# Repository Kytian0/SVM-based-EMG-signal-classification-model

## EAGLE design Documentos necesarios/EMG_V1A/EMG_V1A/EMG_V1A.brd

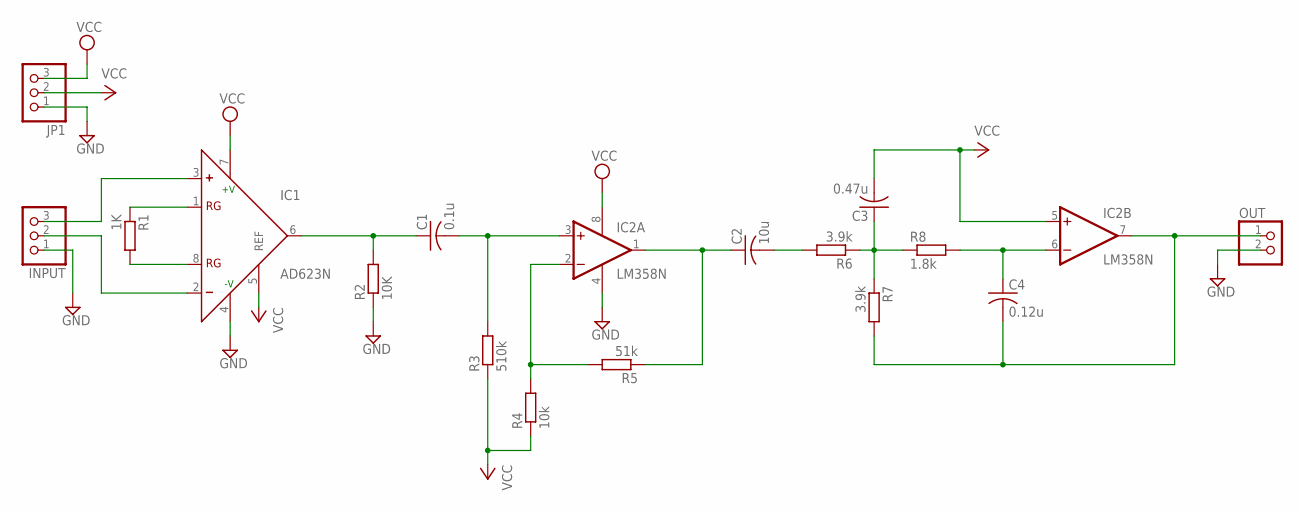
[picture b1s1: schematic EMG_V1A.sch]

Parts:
C1: 0.1u; C050-030X075
C2: 10u; C050-030X075
C3: 0.47u; C050-030X075
C4: 0.12u; C050-030X075
IC1: AD623N; DIL08
IC2: LM358N; DIL08
INPUT: PINHD-1X3; 1X03
JP1: PINHD-1X3; 1X03
OUT: PINHD-1X2; 1X02
R1: 1K; 0204/7
R2: 10K; 0204/7
R3: 510k; 0204/7
R4: 10k; 0204/7
R5: 51k; 0204/7
R6, R7: 3.9k; 0204/7
R8: 1.8k; 0204/7

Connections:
GND: IC1.4 (-V), IC2.4 (V-), INPUT.1, JP1.1, OUT.2, R2.1
unnamed: IC1.1 (RG), R1.1
unnamed: IC1.8 (RG), R1.2
unnamed: IC1.3 (+), INPUT.3
unnamed: IC1.2 (-), INPUT.2
unnamed: C1.1, IC1.6 (OUT), R2.2
unnamed: C1.2, IC2.3 (+IN), R3.2
unnamed: IC2.2 (-IN), R4.2, R5.2
unnamed: C2.2, R6.2
unnamed: C2.1, IC2.1 (OUT), R5.1
unnamed: C3.1, R6.1, R7.1, R8.1
unnamed: C4.1, IC2.6 (-IN), R8.2
unnamed: C4.2, IC2.7 (OUT), OUT.1, R7.2
VCC: C3.2, IC1.5 (REF), IC1.7 (+V), IC2.5 (+IN), IC2.8 (V+), JP1.2, JP1.3, R3.1, R4.1

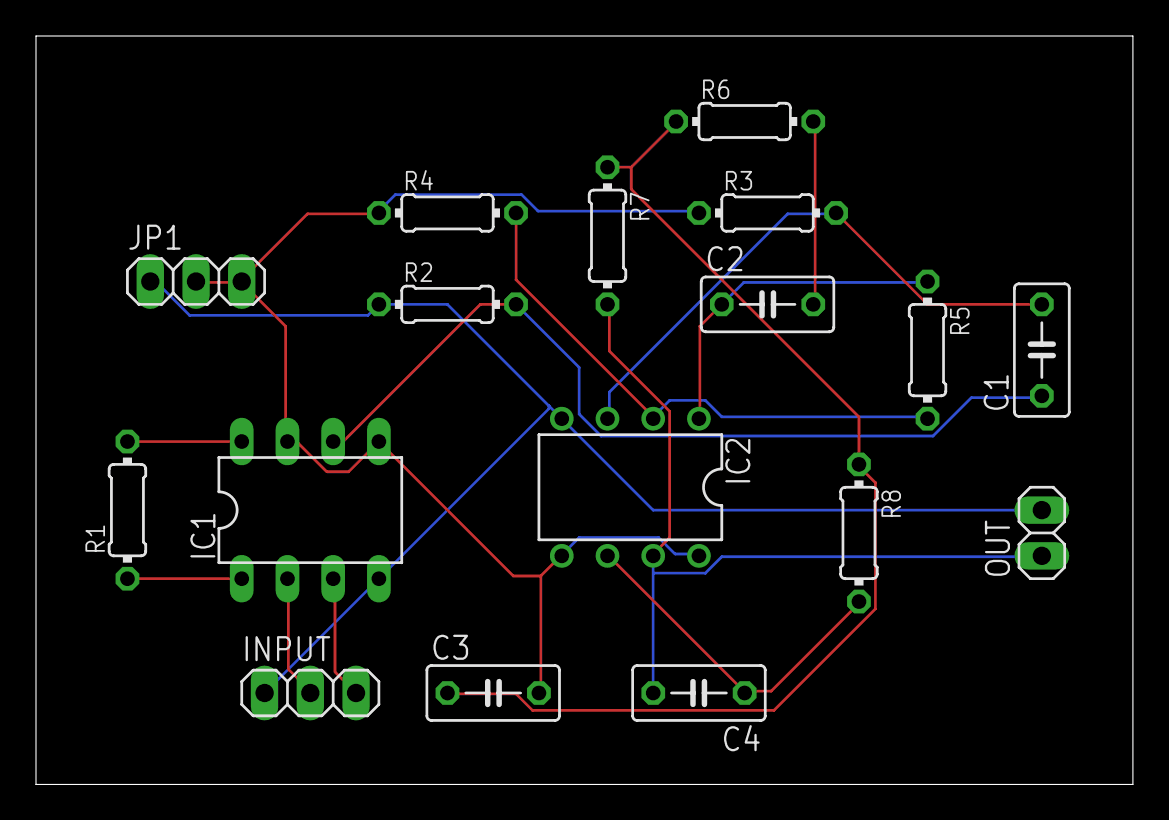
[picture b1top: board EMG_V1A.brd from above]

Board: 2 copper layers, 60.9 x 41.6 mm, 17 parts (0 on the bottom side), 14 nets.
